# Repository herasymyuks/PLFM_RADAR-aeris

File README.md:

# AERIS-10: Open Source Pulse Linear Frequency Modulated Phased Array Radar

)

AERIS-10 is an open-source, low-cost 10.5 GHz phased array radar system featuring Pulse Linear Frequency Modulated (LFM) modulation. Available in two versions (3km and 20km range), it's designed for researchers, drone developers, and serious SDR enthusiasts who want to explore and experiment with phased array radar technology.

## 📡 Overview

The AERIS-10 project aims to democratize radar technology by providing a fully open-source, modular, and hackable radar system. Whether you're a university researcher, a drone startup, or an advanced maker, AERIS-10 offers a platform for experimenting with beamforming, pulse compression, Doppler processing, and target tracking.

## 🔬 Key Features

- **Open Source Hardware & Software** - Complete schematics, PCB layouts, firmware, and software available
- **Dual Version Availability**:
  - **AERIS-10N (Nexus)**: 3km range with 8x16 patch antenna array
  - **AERIS-10X (Extended)**: 20km range with 32x16 dielectric-filled slotted waveguide array
- **Full Electronic Beam Steering** - ±45° electronic steering in elevation and azimuth
- **Advanced Signal Processing** - On-board FPGA handles pulse compression, Doppler FFT, MTI, and CFAR
- **Python GUI** - User-friendly interface with map integration
- **GPS/IMU Integration** - Real-time position and attitude correction
- **Modular Design** - Separate power management, frequency synthesis, and RF boards

## 🏗️ System Architecture

### Hardware Components

The AERIS-10 main sub-systems are:

- **Power Management Board** - Supplies all necessary voltage levels to the electronics components with proper filtering and sequencing (sequencing ensured by the microcontroller)

- **Frequency Synthesizer Board** - Uses a high-performance Low Jitter Clock Generator (AD9523-1) that supplies phase-aligned clock references for:
  - RX and TX Frequency Synthesizers (ADF4382)
  - DAC
  - ADC
  - FPGA

- **Main Board** containing:
  - **DAC** - Generates the RADAR Chirps
  - **2x Microwave Mixers (LT5552)** - For up-conversion and IF-down-conversion
  - **4x 4-Channel Phase Shifters (ADAR1000)** - For RX and TX chain beamforming
  - **16x Front End Chips (ADTR1107)** - Used for both Low Noise Amplifying (RX) and Power Amplifying (TX) stages
  - **XC7A50T-2FTG256I FPGA** (per the Main Board schematic, U42; earlier documentation said XC7A100T — see `docs/FPGA/FPGA_PROJECT_RECONSTRUCTION.md`) - Handles RADAR Signal Processing:
    - PLFM Chirps generation via the DAC
    - Raw ADC data read
    - Automatic Gain Control (AGC)
    - I/Q Baseband Down-Conversion
    - Decimation
    - Filtering
    - Forward FFT
    - Pulse Compression
    - Doppler, MTI and CFAR processing
    - USB Interface
  - **STM32F746xx Microcontroller** - Used for:
    - Power-up and power-down sequencing (see Power Management Excel File)
    - FPGA communication
    - Setup and Interface with:
      - Clock Generator (AD9523-1)
      - 2x Frequency Synthesizers (ADF4382)
      - 4x 4-Channel Phase Shifters (ADAR1000) for RADAR pulse sequencing
      - 2x ADS7830 ADCs (on Power Amplifier Boards) for Idq measurement
      - 2x DAC5578 (on Power Amplifier Boards) for Vg control
      - GPS module for GUI map centering
      - GY-85 IMU for pitch/roll correction of target coordinates
      - BMP180 Barometer
      - Stepper Motor
      - 8x ADS7830 Temperature Sensors for cooling fan control
      - RF switches

- **16x Power Amplifier Boards** - Used only for AERIS-10E version, featuring 10Watt QPA2962 GaN amplifier for extended range

- **Antenna Arrays**:
  - **AERIS-10N (Nexus)** - 8x16 patch antenna array
  - **AERIS-10X (Extended)** - 32x16 dielectric-filled slotted waveguide antenna array

- **Miscellaneous Components**:
  - Slip-Ring
  - Stepper Motor and drivers
  - Cooling Fans
  - Enclosure) 

### Processing Pipeline

1. **Waveform Generation** - DAC creates LFM chirps
2. **Up/Down Conversion** - LT5552 mixers handle frequency translation
3. **Beam Steering** - ADAR1000 phase shifters control 16 elements
4. **Signal Processing (FPGA)**:
   - Raw ADC data capture
   - I/Q baseband down-conversion
   - Decimation & filtering (CIC/FIR)
   - Pulse compression
   - Doppler FFT processing
   - MTI & CFAR detection
5. **System Management (STM32)**:
   - Power sequencing
   - Peripheral configuration
   - GPS/IMU integration
   - Stepper motor control
6. **Visualization (Python GUI)**:
   - Real-time target plotting
   - Map integration
   - Radar control interface

## 📊 Technical Specifications

| Parameter | AERIS-10N (Nexus) | AERIS-10X (Extended) |
|-----------|-------------------|----------------------|
| **Frequency** | 10.5 GHz | 10.5 GHz |
| **Max Range** | 3 km | 20 km |
| **Antenna** | 8x16 Patch Array | 32x16 Slotted Waveguide |
| **Beam Steering** | Electronic (±45°) | Electronic (±45°) |
| **Mechanical Scan** | 360° (stepper motor) | 360° (stepper motor) |
| **Output Power** | ~1Wx16 | 10Wx16 (GaN amplifier) |
| **Processing** | FPGA + STM32 | FPGA + STM32 |

## 🚀 Getting Started

### Prerequisites

- Basic understanding of radar principles
- Experience with PCB assembly (for hardware build)
- Python 3.8+ for the GUI software
- FPGA development tools (Vivado) for signal processing modifications

### Hardware Assembly

1. **Order PCBs**: the designer-released EAGLE export does not exist in `4_Schematics and Boards Layout/4_7_Production Files` (only the Synthesizer P&P/BOM). KiCad-converted manufacturing packages (Gerber, drill, drawings, STEP, DRC) for all four boards are in `engineering/PCB/<BOARD>/` (status in each README — Main and Power Board layouts are unfinished in the source); BETA completions in `beta/pcb/`.
2. **Source Components**: bills of materials with reference designators in `docs/BOM/` (no manufacturer part numbers in the source schematics; BETA BOMs with proposed MPNs in `beta/pcb/`).
3. **Assembly**: `engineering/ASSEMBLY/ASSEMBLY_SEQUENCE.md`, `PARTS_LIST.md` and the CONCEPTUAL exploded view (the `10_docs/assembly_guide.md` referenced earlier was never committed).
4. **Antenna**: no antenna CAD exists in the repository; a PROPOSED 16×8 patch-array panel (KiCad) is in `engineering/DESIGN/ANTENNA/`.
5. **Enclosure**: no enclosure files exist (the `10_docs/Hardware/Enclosure` folder referenced earlier was never committed); a PROPOSED head/pedestal design (FreeCAD/STEP, drawings) is in `engineering/DESIGN/MECHANICAL/`.

> **Reconstruction status (2026-10-09):** see `docs/AERIS10_ENGINEERING_BUILD_MANUAL.md` (master manual), `engineering/DRAWING_REGISTER.md` and `beta/README.md`. Run `bash tools/run_all_checks.sh` for the current validation state.

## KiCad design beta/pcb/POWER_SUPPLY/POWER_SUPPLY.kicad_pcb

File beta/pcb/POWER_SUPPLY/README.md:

# Power Supply Board (PowerBoard) — BETA board

Project AERIS-10 · `beta/pcb/POWER_SUPPLY/` · 2026-10-09 · **Status: BETA — KiCad/Freerouting-routed, DRC-checked, NOT complete (89 connections still open, see `UNROUTED.md`), not reviewed by the original designer, not fabricated.**

Source of this copy: `engineering/PCB/POWER_SUPPLY/kicad/POWER_SUPPLY.kicad_pcb` (kicad-cli EAGLE import of `PowerBoard.brd`; 2 layers, 280 × 300 mm). The source layout was unfinished: 309 airwires and 132 of 320 footprints parked outside the outline (y = +77 … +701 mm).

## 1. Before / after

| Check | Before (engineering/PCB conversion) | After (BETA) |
|---|---|---|
| unconnected_items | 308 | 89 |
| clearance | 53 | 56 |
| drill_out_of_range | 8 | 8 |
| isolated_copper | 4 | 0 |
| silk_over_copper | 40 | 168 |
| silk_overlap | 22 | 65 |
| solder_mask_bridge | 8 | 8 |
| track_dangling | 4 | 2 |
| via_dangling | 0 | 20 |
| zones_intersect | 21 | 1 |
| **DRC violations total** | 160 | 328 |

Unconnected items 308 → **89** (−71 %). Footprints outside the outline 132 → **0**. Reports: `exports/reports/DRC_report.txt|json`.

## 2. What was changed (chronological, all logged)

| # | Change | Result | Tool / log |
|---|---|---|---|
| 1 | Netclass `Default`: track 0.25 mm, clearance 0.2 mm, via 0.5/0.3 mm (routing rule for new copper only) | — | `POWER_SUPPLY.kicad_pro` |
| 2 | 110 parts placed inside the outline in 29 net clusters next to the inside parts they connect to (1 mm grid, 3 mm edge margin, no overlap with existing parts/tracks/pours); 22 KK-254 connectors (`22-23-2021`) placed on the nearest board edge | 132 → 0 outside | `tools/beta_place_outside.py`, `placement_moves.json`, `placement_moves_connectors.json` |
| 3 | Freerouting 2.5.0 pass 1 (20 passes, existing 916 tracks/vias exported `(type fix)`), SES merged additively | +1336 tracks, +168 vias; unconnected 308 → 102 | `POWER_SUPPLY.dsn/.ses`, `freerouting.log`, `ses_merge.json` |
| 4 | 45 overlapping same-net zones re-prioritised; board-wide B.Cu GND zone `BETA_GND_plane_B.Cu` added (priority 0 — the EAGLE B.Cu GND polygon already covers the board, so it only fills remaining gaps) | zones_intersect 21 → 1 | `tools/beta_zone_priorities.py`, `tools/beta_add_plane.py` |
| 5 | Straight same-net bridges for the gaps in the DRC list, DRC, revert of every bridge that caused a clearance/crossing violation | 102 tried, 29 kept; 102 → 96 | `tools/beta_bridge_unconnected.py`, `bridges_pass1.json` |
| 6 | Freerouting pass 2 on the bridged board (12 passes) | +36 tracks, +3 vias; 96 → 96 | `POWER_SUPPLY_pass2.ses`, `freerouting_pass2.log`, `ses_merge_pass2.json` |
| 7 | GND stitching: vias where B.Cu GND islands overlap F.Cu GND fills, via next to unconnected GND pads; DRC-violating ones reverted | 50 tried, 22 kept; 96 → 89 | `tools/beta_gnd_stitch.py`, `stitch_gnd.json` |
| 8 | Refill, DRC, package export | | `tools/beta_drc.sh`, `tools/beta_export_package.sh`, `exports/EXPORT_LOG.md` |

## 3. What remains

* **89 unconnected items** — listed with reasons and a manual procedure in `UNROUTED.md` (49 GND, 10 VIN, rest on regulator outputs). Root causes: the EAGLE design distributes VIN/GND through separate local pours joined only by airwires (an autorouter does not connect pour to pour), and the autorouted bottom tracks fragment the B.Cu GND plane.
* DRC (`exports/reports/DRC_report.txt`): clearance 56 (0.15 mm pad-to-pad inside the ADM7151/TPS7A83 footprints and 3 N$ tracks of the source — footprint/library level, EAGLE DRU allowed 0.15 mm there), drill_out_of_range 8 (0.254 mm via-pads in the TPS7A8300 footprint vs DRU 0.3 mm min drill — footprint level, fab to confirm), silk_over_copper 168 / silk_overlap 65 (reference texts of the parts placed by script sit on their own pads — cosmetic, to be tidied with `tools/beta_silk_nudge.py` once routing is final), via_dangling 20 (autorouter vias whose second-side wire was dropped — remove with *Cleanup tracks & vias* once routing is final), solder_mask_bridge 8, track_dangling 2, zones_intersect 1.
* Placement by script is topological, not thermal/EMC: the regulator clusters sit where free space was nearest to their connectors. **A designer must review the placement** (inductor orientation, input/output capacitor proximity, heat spreading) before any routing clean-up.
* 24 pins without net in the schematic (`engineering/ELECTRICAL/netlists/POWER_SUPPLY_unresolved_connections.md`: TPS7A8300 feedback-select pins, LM2662 FC/OSC) are not a layout issue but must be dispositioned before fabrication.

## 4. Files

`POWER_SUPPLY.kicad_pcb` / `.kicad_pro` (BETA board), `BOM_POWER_SUPPLY_beta.csv` (7 HIGH / 18 MEDIUM / 3 LOW / 0 EMPTY lines), `FAB_NOTES.md`, `UNROUTED.md`, logs listed above, `exports/`.

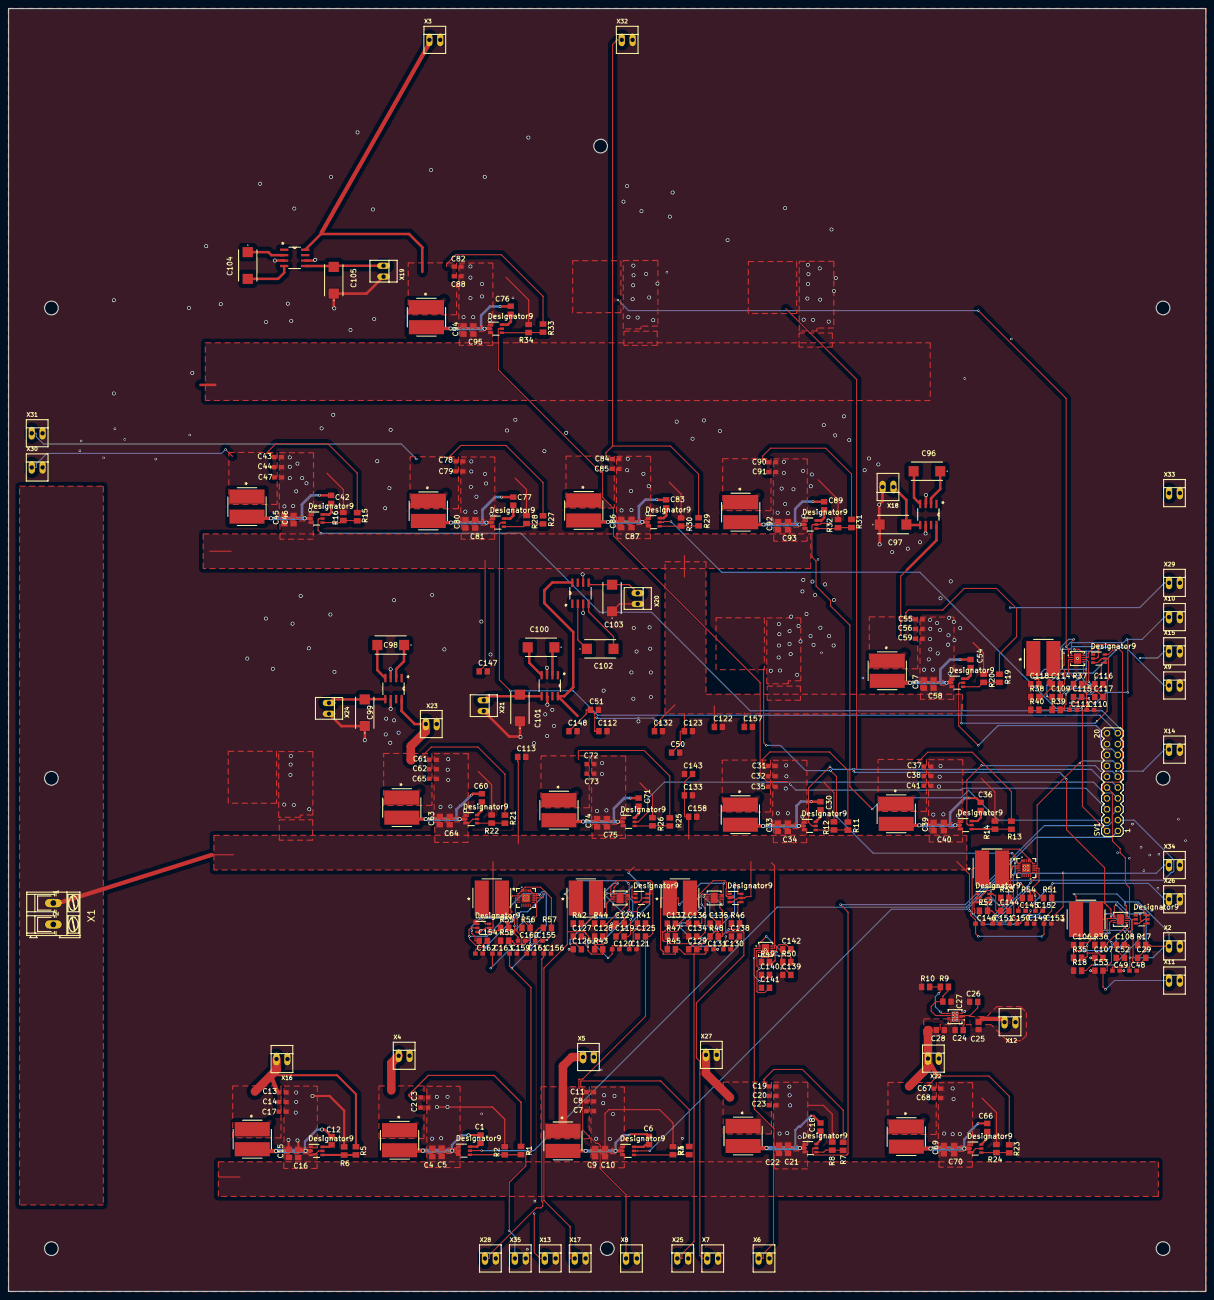
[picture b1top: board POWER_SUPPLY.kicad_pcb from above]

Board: 2 copper layers, 280.0 x 300.0 mm, 320 parts (0 on the bottom side), 156 nets.

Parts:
C1, C6, C12, C18, C29, C30, C36, C42, C54, C60, C66, C71, C76, C77, C83, C89, C109, C119, C129, C144, C154: 0.1µF; C0805
C2, C3, C7, C8, C11, C13, C14, C17, C19, C20, C23, C31, C32, C35, C37, C38, C41, C43, C44, C47, C48, C49, C55, C56, C59, C61, C62, C65, C67, C68, C72, C73, C78, C79, C82, C84, C85, C88, C90, C91, C110, C111, C120, C121, C130, C131, C145, C146, C149, C155, C156, C159: 22µF; C0603
C4, C5, C9, C10, C15, C16, C21, C22, C24, C25, C28, C33, C34, C39, C40, C45, C46, C50, C51, C52, C53, C57, C58, C63, C64, C69, C70, C74, C75, C80, C81, C86, C87, C92, C93, C94, C95, C108, C112, C113, C114, C115, C118, C122, C123, C124, C125, C128, C132, C133, C134, C135, C138, C139, C140, C143, C147, C148, C157, C158: 10µF; C0805
C26, C27, C106, C107, C116, C117, C126, C127, C136, C137, C141, C142: 1µF; C0805
C96, C97, C98, C99, C100, C101, C102, C103, C104, C105: T521W476M020ATE045; T521W
C150, C152, C160, C162: 10nF; C0603
C151, C153, C161, C163: 10µF; C0603
R1: 3.09k; M0805
R2, R4, R6, R8, R10, R12, R14, R16, R18, R20, R22, R24, R26, R28, R30, R32, R34, R36, R38, R40, R42, R44, R46, R48, R50, R52, R56: 10k; M0805
R3: 13.7k; M0805
R5, R7, R11, R13, R15, R19: 32.2k; M0805
R9, R35, R43, R47: 12k; M0805
R17, R23, R25, R27, R29, R31, R37, R41, R45, R51, R55: 56.2k; M0805
R21: 34.8k; M0805
R33: 61.9k; M0805
R39: 2k; M0805
R49: 23.4k; M0805
R53, R57: 35.7k; M0805
R54, R58: 11.5k; M0805
SV1: MA10-2
U1, U2, U3, U4, U6, U7, U8, U9, U10, U11, U12, U13, U14, U15, U16, U17, U24, U26, U28, U31, U33: TPS562208DDCT; DDC0006A_N
U5, U23, U25, U27, U29, U30: ADM7151ACPZ-04-R7; CP_8_11_ADI
U18, U19, U20, U21, U22: LM2662MX/NOPB; M08A
U32, U34: TPS7A8300RGRR; RGR20_2P05X2P05_TEX
U$1, U$2: 2.2µH; IND_VLP8040T-1R0N_TDK
U$3, U$4, U$5, U$6, U$7, U$8, U$9, U$10, U$11, U$12, U$13, U$14, U$15, U$16, U$17, U$18, U$19, U$20, U$21: 3.3µH; IND_VLP8040T-1R0N_TDK
UNK_HOLE_0: dummyfp0
UNK_HOLE_1: dummyfp1
UNK_HOLE_2: dummyfp2
UNK_HOLE_3: dummyfp3
UNK_HOLE_4: dummyfp4
UNK_HOLE_5: dummyfp5
UNK_HOLE_6: dummyfp6
UNK_HOLE_7: dummyfp7
X1: AK300_2
X2, X3, X4, X5, X6, X7, X8, X9, X10, X11, X12, X13, X14, X15, X16, X17, X18, X19, X20, X21, X22, X23, X24, X25, X26, X27, X28, X29, X30, X31, X32, X33, X34, X35: 22-23-2021

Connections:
+1V0_FPGA: C2.1, C3.1, R1.2, U$1.1, X4.1
+1V8_CLOCK: C115.2, U25.2, X10.1
+1V8_FPGA: C7.1, C8.1, C11.1, R3.2, U$2.1, X5.1
+3V3: C13.1, C14.1, C17.1, R5.2, U$3.1, X16.1
+3V3_ADAR_12: C31.1, C32.1, C35.1, R11.2, U$6.1, X14.1
+3V3_ADAR_34: C37.1, C38.1, C41.1, R13.2, U$7.1, X15.1
+3V3_ADTR: C149.1, R53.2, U32.1, U32.19, U32.20, X34.1
+3V3_AN: C25.2, U5.2, X12.1
+3V3_CLOCK: C53.2, U23.2, X11.1
+3V3_FPGA: C19.1, C20.1, C23.1, R7.2, U$4.1, X27.1
+3V3_LO_1: C125.2, U27.2, X8.1
+3V3_LO_2: C135.2, U29.2, X7.1
+3V3_SW: C55.1, C56.1, C59.1, R19.2, U18.8, U$10.1, X29.1
+3V3_VDD_SW: C43.1, C44.1, C47.1, R15.2, U$8.1, X30.1
+3V3_XO: C159.1, R57.2, U34.1, U34.19, U34.20, X35.1
+3V4: C61.1, C62.1, C65.1, R21.2, U19.8, U$11.1, X23.1
+5V0_0: C28.2, C67.1, C68.1, R23.2, U5.7, U5.8, U$12.1, X22.1
+5V0_1: C48.1, C49.1, C108.2, R17.2, U23.8, U$5.1, X2.1
+5V0_2: C110.1, C111.1, C118.2, R37.2, U25.8, U$9.1, X9.1
+5V0_3: C120.1, C121.1, C128.2, R41.2, U27.7, U27.8, U$18.1, X17.1
+5V0_4: C130.1, C131.1, C138.2, R45.2, U29.7, U29.8, U$19.1, X25.1
+5V0_5: C155.1, C156.1, C163.1, R55.2, U34.14, U34.15, U34.16, U34.17, U$21.1, X28.1
+5V0_ADAR: C72.1, C73.1, R25.2, U20.8, U21.8, U$13.1, X13.1
+5V0_ADTR: C145.1, C146.1, C153.1, R51.2, U32.15, U32.16, U32.17, U$20.1, X26.1
+5V0_LO: C140.2, U30.2, X6.1
+5V0_PA_1: C78.1, C79.1, R27.2, U$14.1, X31.1
+5V0_PA_2: C84.1, C85.1, R29.2, U$15.1, X32.1
+5V0_PA_3: C90.1, C91.1, R31.2, U$16.1, X33.1
+5V5_PA: C82.1, C88.1, R33.2, U22.8, U$17.1, X3.1
-3V3_SW: C97.2, U18.5, X18.1
-3V4: C99.2, U19.5, X24.1
-5V0_ADAR12: C101.2, U20.5, X21.1
-5V0_ADAR34: C103.2, U21.5, X20.1
-5V5_PA: C105.2, U22.5, X19.1
EN_+1V0_FPGA: SV1.1, U1.5
EN_+1V8_CLOCK: SV1.8, U25.7
EN_+1V8_FPGA: SV1.3, U2.5
EN_+3V3_ADAR12: SV1.9, U6.5
EN_+3V3_ADAR34: SV1.11, U7.5
EN_+3V3_ADTR: SV1.13, U32.14
EN_+3V3_CLOCK: SV1.10, U23.7
EN_+3V3_FPGA: SV1.5, U4.5
EN_+3V3_SW: SV1.15, U10.5
EN_+3V3_VDD_SW: SV1.17, U8.5
EN_+5V0_ADAR: SV1.7, U13.5
EN_+5V0_PA1: SV1.19, U14.5
EN_+5V0_PA2: SV1.2, U15.5
EN_+5V0_PA3: SV1.4, U16.5
EN_+5V5_PA: SV1.6, U17.5
GND: C2.2, C3.2, C4.2, C5.2, C7.2, C8.2, C9.2, C10.2, C11.2, C13.2, C14.2, C15.2, C16.2, C17.2, C19.2, C20.2, C21.2, C22.2, C23.2, C24.1, C25.1, C26.1, C27.1, C28.1, C31.2, C32.2, C33.2, C34.2, C35.2, C37.2, C38.2, C39.2, C40.2, C41.2, C43.2, C44.2, C45.2, C46.2, C47.2, C48.2, C49.2, C50.2, C51.2, C52.1, C53.1, C55.2, C56.2, C57.2, C58.2, C59.2, C61.2, C62.2, C63.2, C64.2, C65.2, C67.2, C68.2, C69.2, C70.2, C72.2, C73.2, C74.2, C75.2, C78.2, C79.2, C80.2, C81.2, C82.2, C84.2, C85.2, C86.2, C87.2, C88.2, C90.2, C91.2, C92.2, C93.2, C94.2, C95.2, C97.1, C99.1, C101.1, C103.1, C105.1, C106.1, C107.1, C108.1, C110.2, C111.2, C112.2, C113.2, C114.1, C115.1, C116.1, C117.1, C118.1, C120.2, C121.2, C122.2, C123.2, C124.1, C125.1, C126.1, C127.1, C128.1, C130.2, C131.2, C132.2, C133.2, C134.1, C135.1, C136.1, C137.1, C138.1, C139.1, C140.1, C141.1, C142.1, C143.1, C145.2, C146.2, C147.2, C148.2, C149.2, C151.2, C152.2, C153.2, C155.2, C156.2, C157.2, C158.2, C159.2, C161.2, C162.2, C163.2, R2.1, R4.1, R6.1, R8.1, R10.1, R12.1, R14.1, R16.1, R18.1, R20.1, R22.1, R24.1, R26.1, R28.1, R30.1, R32.1, R34.1, R36.1, R38.1, R40.1, R42.1, R44.1, R46.1, R48.1, R50.1, R52.1, R54.1, R56.1, R58.1, SV1.12, SV1.14, SV1.16, SV1.18, SV1.20, U1.1, U2.1, U3.1, U4.1, U5.4, U5.9, U6.1, U7.1, U8.1, U9.1, U10.1, U11.1, U12.1, U13.1, U14.1, U15.1, U16.1, U17.1, U18.3, U18.6, U19.3, U19.6, U20.3, U20.6, U21.3, U21.6, U22.3, U22.6, U23.4, U23.9, U24.1, U25.4, U25.9, U26.1, U27.4, U27.9, U28.1, U29.4, U29.9, U30.4, U30.9, U31.1, U32.8, U32.18, U32.21, U33.1, U34.8, U34.18, U34.21, X1.2, X2.2, X3.2, X4.2, X5.2, X6.2, X7.2, X8.2, X9.2, X10.2, X11.2, X12.2, X13.2, X14.2, X15.2, X16.2, X17.2, X18.2, X19.2, X20.2, X21.2, X22.2, X23.2, X24.2, X25.2, X26.2, X27.2, X28.2, X29.2, X30.2, X31.2, X32.2, X33.2, X34.2, X35.2
unnamed: C1.2, U1.2, U$1.2
unnamed: C1.1, U1.6
unnamed: C6.2, U2.2, U$2.2
unnamed: R1.1, R2.2, U1.4
unnamed: C6.1, U2.6
unnamed: R3.1, R4.2, U2.4
unnamed: C12.2, U3.2, U$3.2
unnamed: C12.1, U3.6
unnamed: R5.1, R6.2, U3.4
unnamed: C18.2, U4.2, U$4.2
unnamed: C18.1, U4.6
unnamed: R7.1, R8.2, U4.4
unnamed: C24.2, U5.1
unnamed: C139.2, U30.1
unnamed: C26.2, U5.3
unnamed: C30.2, U6.2, U$6.2
unnamed: C30.1, U6.6
unnamed: R11.1, R12.2, U6.4
unnamed: C36.2, U7.2, U$7.2
unnamed: C36.1, U7.6
unnamed: R13.1, R14.2, U7.4
unnamed: C42.2, U8.2, U$8.2
unnamed: C42.1, U8.6
unnamed: R15.1, R16.2, U8.4
unnamed: R9.1, R10.2, U5.5
unnamed: C29.2, U9.2, U$5.2
unnamed: C27.2, R9.2, U5.6
unnamed: C54.2, U10.2, U$10.2
unnamed: C54.1, U10.6
unnamed: R19.1, R20.2, U10.4
unnamed: C60.2, U11.2, U$11.2
unnamed: C60.1, U11.6
unnamed: R21.1, R22.2, U11.4
unnamed: C66.2, U12.2, U$12.2
unnamed: C66.1, U12.6
unnamed: R23.1, R24.2, U12.4
unnamed: C71.2, U13.2, U$13.2
unnamed: C71.1, U13.6
unnamed: R25.1, R26.2, U13.4
unnamed: C77.2, U14.2, U$14.2
unnamed: C77.1, U14.6
unnamed: R27.1, R28.2, U14.4
unnamed: C83.2, U15.2, U$15.2
unnamed: C83.1, U15.6
unnamed: R29.1, R30.2, U15.4
unnamed: C89.2, U16.2, U$16.2
unnamed: C89.1, U16.6
unnamed: R31.1, R32.2, U16.4
unnamed: C76.2, U17.2, U$17.2
unnamed: C76.1, U17.6
unnamed: R33.1, R34.2, U17.4
unnamed: C98.1, U19.2
unnamed: C98.2, U19.4
unnamed: C96.1, U18.2
unnamed: C96.2, U18.4
unnamed: C100.1, U20.2
unnamed: C100.2, U20.4
unnamed: C102.1, U21.2
unnamed: C102.2, U21.4
unnamed: C104.1, U22.2
unnamed: C104.2, U22.4
unnamed: C141.2, U30.3
unnamed: R49.1, R50.2, U30.5
unnamed: C29.1, U9.6
unnamed: R17.1, R18.2, U9.4
unnamed: C52.2, U23.1
unnamed: C142.2, R49.2, U30.6
unnamed: C106.2, U23.3
unnamed: R35.1, R36.2, U23.5
unnamed: C107.2, R35.2, U23.6
unnamed: C144.2, U31.2, U$20.2
unnamed: C144.1, U31.6
unnamed: C109.2, U24.2, U$9.2
unnamed: C109.1, U24.6
unnamed: R37.1, R38.2, U24.4
unnamed: C114.2, U25.1
unnamed: R51.1, R52.2, U31.4
unnamed: C116.2, U25.3
unnamed: R39.1, R40.2, U25.5
unnamed: C117.2, R39.2, U25.6
unnamed: C154.2, U33.2, U$21.2
unnamed: C150.1, U32.2
unnamed: C119.2, U26.2, U$18.2
unnamed: C119.1, U26.6
unnamed: R41.1, R42.2, U26.4
unnamed: C124.2, U27.1
unnamed: C154.1, U33.6
unnamed: C126.2, U27.3
unnamed: R43.1, R44.2, U27.5
unnamed: C127.2, R43.2, U27.6
unnamed: C150.2, R53.1, R54.2, U32.3
unnamed: C151.1, U32.12
unnamed: C129.2, U28.2, U$19.2
unnamed: C129.1, U28.6
unnamed: R45.1, R46.2, U28.4
unnamed: C134.2, U29.1
unnamed: R55.1, R56.2, U33.4
unnamed: C136.2, U29.3
unnamed: R47.1, R48.2, U29.5
unnamed: C137.2, R47.2, U29.6
unnamed: C152.1, U32.13
unnamed: C160.1, U34.2
unnamed: C160.2, R57.1, R58.2, U34.3
unnamed: C161.1, U34.12
unnamed: C162.1, U34.13
VIN: C4.1, C5.1, C9.1, C10.1, C15.1, C16.1, C21.1, C22.1, C33.1, C34.1, C39.1, C40.1, C45.1, C46.1, C50.1, C51.1, C57.1, C58.1, C63.1, C64.1, C69.1, C70.1, C74.1, C75.1, C80.1, C81.1, C86.1, C87.1, C92.1, C93.1, C94.1, C95.1, C112.1, C113.1, C122.1, C123.1, C132.1, C133.1, C143.2, C147.1, C148.1, C157.1, C158.1, U1.3, U2.3, U3.3, U3.5, U4.3, U6.3, U7.3, U8.3, U9.3, U9.5, U10.3, U11.3, U11.5, U12.3, U12.5, U13.3, U14.3, U15.3, U16.3, U17.3, U24.3, U24.5, U26.3, U26.5, U28.3, U28.5, U30.7, U30.8, U31.3, U31.5, U33.3, U33.5, X1.1

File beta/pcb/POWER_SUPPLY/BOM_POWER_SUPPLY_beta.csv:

item,qty,references,value,deviceset,device,package,manufacturer,mpn,mpn_confidence,dnp,note
1,34,X10 X11 X12 X13 X14 X15 X16 X17 X18 X19 X2 X20 X21 X22 X23 X24 X25 X26 X27 X28 X29 X3 X30 X31 X32 X33 X34 X35 X4 X5 X6 X7 X8 X9,,22-23-2021,,22-23-2021,Molex,22-23-2021,HIGH,no,"KK 254 header, 2 pos"
2,6,U23 U25 U27 U29 U30 U5,,ADM7151ACPZ-04-R7,,CP_8_11_ADI,Analog Devices,ADM7151ACPZ-04-R7,HIGH,no,"ultralow-noise LDO, LFCSP-8"
3,1,X1,,AK300/2,,AK300/2,PTR Messtechnik,AK300/2,HIGH,no,screw terminal 2 pos (library con-ptr500); verify current PTR part code AK300/2-5.0
4,21,C1 C109 C119 C12 C129 C144 C154 C18 C29 C30 C36 C42 C54 C6 C60 C66 C71 C76 C77 C83 C89,0.1µF,C-EU,C0805,C0805,Murata,GRM21BR71H104KA01L,MEDIUM,no,0805 X7R 50 V
5,4,C150 C152 C160 C162,10nF,C-EU,C0603,C0603,Murata,GRM188R71H103KA01D,MEDIUM,no,0603 X7R 50 V
6,60,C10 C108 C112 C113 C114 C115 C118 C122 C123 C124 C125 C128 C132 C133 C134 C135 C138 C139 C140 C143 C147 C148 C15 C157 C158 C16 C21 C22 C24 C25 C28 C33 C34 C39 C4 C40 C45 C46 C5 C50 C51 C52 C53 C57 C58 C63 C64 C69 C70 C74 C75 C80 C81 C86 C87 C9 C92 C93 C94 C95,10µF,C-EU,C0805,C0805,Murata,GRM21BR61E106KA73L,MEDIUM,no,0805 X5R 25 V
7,4,C151 C153 C161 C163,10µF,C-EU,C0603,C0603,Murata,GRM188R61E106MA73D,MEDIUM,no,0603 X5R 25 V
8,12,C106 C107 C116 C117 C126 C127 C136 C137 C141 C142 C26 C27,1µF,C-EU,C0805,C0805,Murata,GRM21BR71H105KA12L,MEDIUM,no,0805 X7R 50 V
9,52,C11 C110 C111 C120 C121 C13 C130 C131 C14 C145 C146 C149 C155 C156 C159 C17 C19 C2 C20 C23 C3 C31 C32 C35 C37 C38 C41 C43 C44 C47 C48 C49 C55 C56 C59 C61 C62 C65 C67 C68 C7 C72 C73 C78 C79 C8 C82 C84 C85 C88 C90 C91,22µF,C-EU,C0603,C0603,Murata,GRM188R60J226MEA0D,MEDIUM,no,0603 X5R 6.3 V — rail voltage to be verified
10,5,U18 U19 U20 U21 U22,,LM2662MX/NOPB,,M08A,Texas Instruments,LM2662MX/NOPB,HIGH,no,"switched-capacitor inverter, SOIC-8"
11,1,SV1,,MA10-2,,MA10-2,generic,TSW-110-07-G-D,LOW,no,EAGLE con-lstb MA10-2 = 2×10 pin header 2.54 mm; Samtec TSW-110-07-G-D proposed
12,2,U$1 U$2,2.2µH,POWER_INDUCTOR,,IND_VLP8040T-1R0N_TDK,TDK,VLP8040T-2R2M,MEDIUM,no,footprint is the VLP8040T 1R0N (1 µH) variant; value 2.2uH → same series part proposed
13,19,U$10 U$11 U$12 U$13 U$14 U$15 U$16 U$17 U$18 U$19 U$20 U$21 U$3 U$4 U$5 U$6 U$7 U$8 U$9,3.3µH,POWER_INDUCTOR,,IND_VLP8040T-1R0N_TDK,TDK,VLP8040T-3R3M,MEDIUM,no,footprint is the VLP8040T 1R0N (1 µH) variant; value 3.3uH → same series part proposed
14,27,R10 R12 R14 R16 R18 R2 R20 R22 R24 R26 R28 R30 R32 R34 R36 R38 R4 R40 R42 R44 R46 R48 R50 R52 R56 R6 R8,10k,R-EU_,M0805,M0805,Yageo,RC0805FR-0710KL,MEDIUM,no,1 % thick film
15,2,R54 R58,11.5k,R-EU_,M0805,M0805,Yageo,RC0805FR-0711K5L,MEDIUM,no,1 % thick film
16,4,R35 R43 R47 R9,12k,R-EU_,M0805,M0805,Yageo,RC0805FR-0712KL,MEDIUM,no,1 % thick film
17,1,R3,13.7k,R-EU_,M0805,M0805,Yageo,RC0805FR-0713K7L,MEDIUM,no,1 % thick film
18,1,R49,23.4k,R-EU_,M0805,M0805,Yageo,,LOW,no,non-E24/E96 value 23.4 Ω (nearest standard 2.32e+04 Ω) — value substitution is a design decision (Yageo RC0805FR-07 series)
19,1,R39,2k,R-EU_,M0805,M0805,Yageo,RC0805FR-072KL,MEDIUM,no,1 % thick film
20,1,R1,3.09k,R-EU_,M0805,M0805,Yageo,RC0805FR-073K09L,MEDIUM,no,1 % thick film
21,6,R11 R13 R15 R19 R5 R7,32.2k,R-EU_,M0805,M0805,Yageo,,LOW,no,non-E24/E96 value 32.2 Ω (nearest standard 3.24e+04 Ω) — value substitution is a design decision (Yageo RC0805FR-07 series)
22,1,R21,34.8k,R-EU_,M0805,M0805,Yageo,RC0805FR-0734K8L,MEDIUM,no,1 % thick film
23,2,R53 R57,35.7k,R-EU_,M0805,M0805,Yageo,RC0805FR-0735K7L,MEDIUM,no,1 % thick film
24,11,R17 R23 R25 R27 R29 R31 R37 R41 R45 R51 R55,56.2k,R-EU_,M0805,M0805,Yageo,RC0805FR-0756K2L,MEDIUM,no,1 % thick film
25,1,R33,61.9k,R-EU_,M0805,M0805,Yageo,RC0805FR-0761K9L,MEDIUM,no,1 % thick film
26,10,C100 C101 C102 C103 C104 C105 C96 C97 C98 C99,,T521W476M020ATE045,,T521W,KEMET,T521W476M020ATE045,HIGH,no,"polymer tantalum 47 µF 20 V, case W"
27,21,U1 U10 U11 U12 U13 U14 U15 U16 U17 U2 U24 U26 U28 U3 U31 U33 U4 U6 U7 U8 U9,,TPS562208DDCT,,DDC0006A_N,Texas Instruments,TPS562208DDCT,HIGH,no,"2 A buck converter, SOT-23-6"
28,2,U32 U34,,TPS7A8300RGRR,,RGR20_2P05X2P05_TEX,Texas Instruments,TPS7A8300RGRR,HIGH,no,"2 A LDO, VQFN-20"

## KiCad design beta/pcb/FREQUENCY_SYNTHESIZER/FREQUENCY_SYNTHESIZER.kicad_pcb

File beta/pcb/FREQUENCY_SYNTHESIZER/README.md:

# Frequency Synthesizer (Clocks_Freq_Synth_board) — BETA board

Project AERIS-10 · `beta/pcb/FREQUENCY_SYNTHESIZER/` · 2026-10-09 · **Status: BETA — KiCad-checked, silkscreen-cleaned, not reviewed by the original designer, not fabricated.**

Source of this copy: `engineering/PCB/FREQUENCY_SYNTHESIZER/kicad/FREQUENCY_SYNTHESIZER.kicad_pcb` (kicad-cli EAGLE import of `Clocks_Freq_Synth_board.brd`). Copper was **not modified** (fully routed in the source, 0 unconnected).

## 1. Before / after

| Check | Before (engineering/PCB conversion) | After (BETA) |
|---|---|---|
| unconnected_items | 0 | 0 |
| courtyards_overlap | 7 | 7 |
| silk_over_copper | 199 | 199 |
| silk_overlap | 199 | 199 |
| solder_mask_bridge | 199 | 199 |
| track_dangling | 35 | 35 |
| **DRC violations total** | 639 | 639 |

The silkscreen and mask counts are capped at 199 by KiCad; uncapped measurements and the classification of every type are in `DRC_DISPOSITION.md` (cosmetic silk/mask vs. real). Real items for review: 7 courtyard overlaps.

## 2. What was changed

| # | Change | Tool / log |
|---|---|---|
| 1 | 43 silkscreen reference texts moved to the nearest free position (≤ 3 mm, 0.05 mm step; copper untouched) | `tools/beta_silk_nudge.py`, `silk_nudges.json`; 103 texts still in conflict → `silk_conflicts_remaining.json` |
| 2 | Zones refilled, DRC re-run, package exported | `tools/beta_drc.sh`, `tools/beta_export_package.sh`, `exports/EXPORT_LOG.md` |

## 3. What remains

See `DRC_DISPOSITION.md`: 7 courtyard overlaps (review), 35 GND arc stubs (cosmetic), silk/mask items (cosmetic / fab CAM). Recommendation for the production revision: hide 0201 reference designators on silk.

## 4. Files

`FREQUENCY_SYNTHESIZER.kicad_pcb` / `.kicad_pro` / `_from_eagle.kicad_dru`, `BOM_FREQUENCY_SYNTHESIZER_beta.csv` (10 HIGH / 22 MEDIUM / 6 LOW / 2 EMPTY lines), `FAB_NOTES.md` (6-layer RO4350B/FR-4 stack-up proposal, 50 Ω / 100 Ω geometry measured w = 0.204 mm, s = 0.26 mm), `DRC_DISPOSITION.md`, `exports/`.

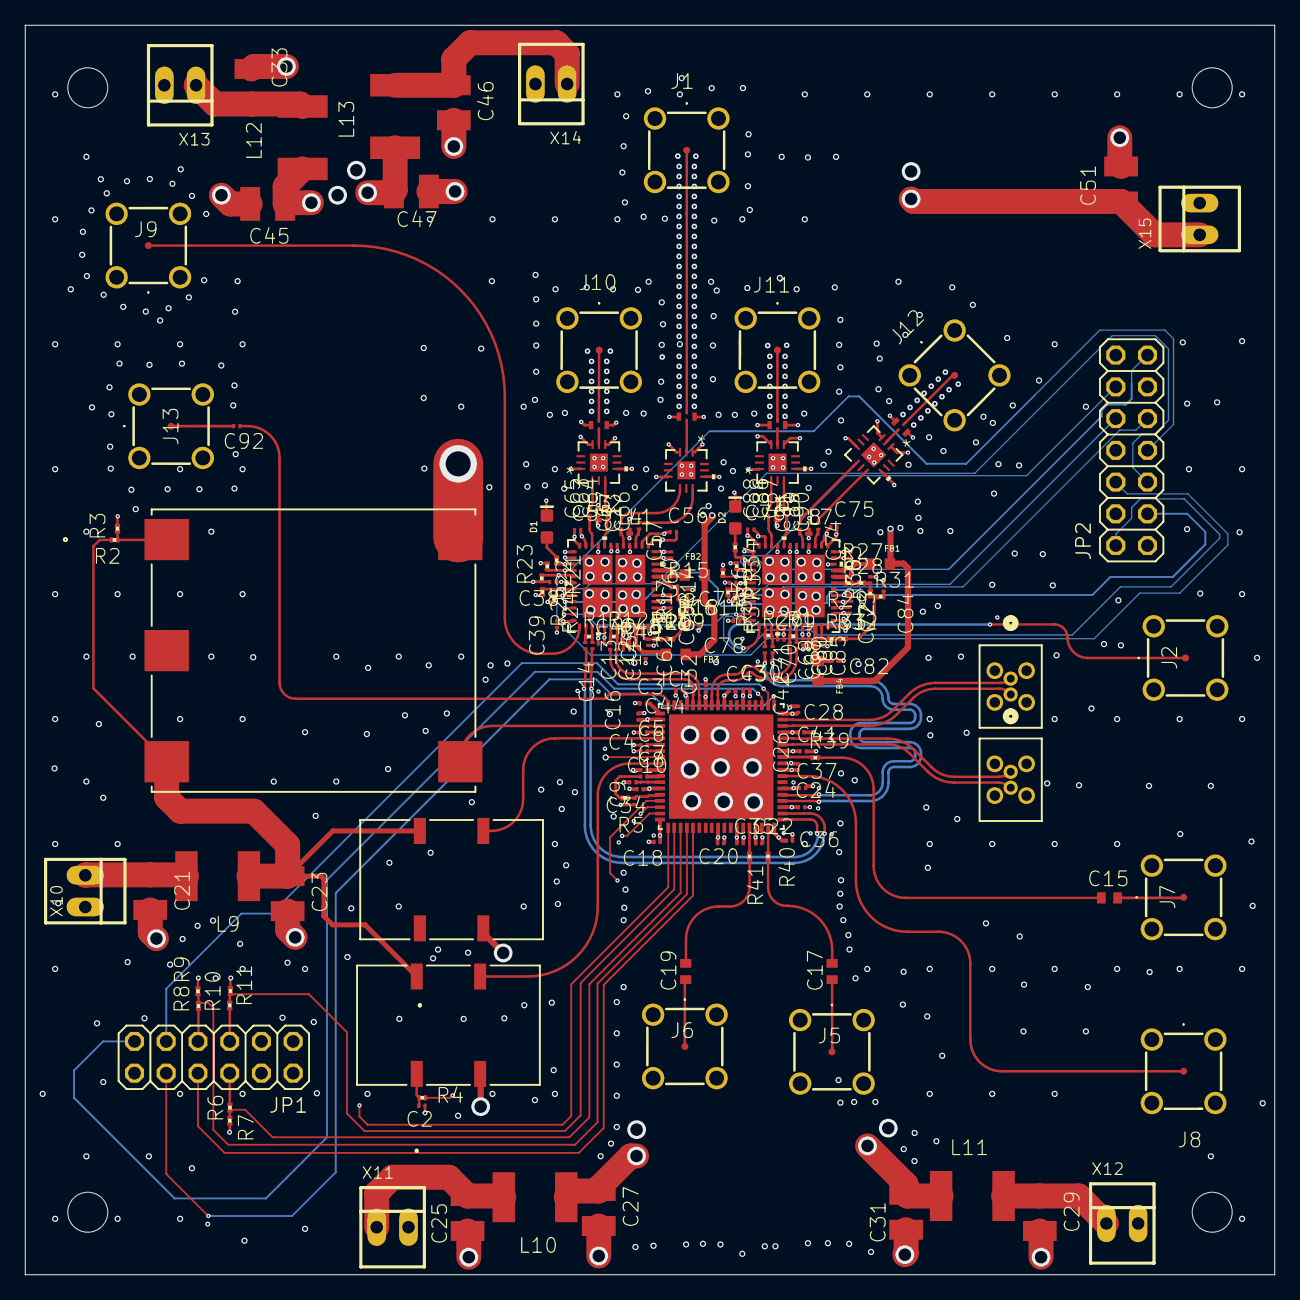
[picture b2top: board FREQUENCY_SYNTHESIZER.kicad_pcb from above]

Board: 6 copper layers, 100.0 x 100.0 mm, 188 parts (0 on the bottom side), 134 nets.

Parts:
C1, C62, C63, C85, C86, C89: 10pF; C0201
C2, C6: 0.33µF; C0201
C3: 0.47µf; C0201
C4, C5, C7: C0201
C8: 1000pF; C0201
C9, C10: 0.47µF; C0201
C11, C12, C13, C14, C59, C68, C69, C70, C71, C82: 1µF; C0201
C15, C17, C19: 10nF; C0402
C16, C18, C20, C22, C24, C26, C28, C30, C32, C34, C35, C36, C37, C41, C42, C43, C44, C64, C65, C66, C67, C87, C88, C90, C91: 0.1µF; C0201
C21, C25, C29, C33, C46, C51: 22µF; C1210
C23, C27, C31, C45, C47: 10µF; C1210
C38, C39, C40, C48, C49, C50, C55, C56, C57, C58, C72, C73, C74, C75, C76, C77, C78, C79, C80, C81: 4.7µF; C0201
C60, C83: 31pF; C0201
C61, C84: 10nF; C0201
C92: 0.1µf; C0201
D1, D2: Green; LED-0603
FB1, FB2, FB3, FB4: FBMH1608HL601-T; BEADC1608X90N
IC1: AD9523BCPZ; QFN50P1000X1000X100-73N
J1, J2, J5, J6, J7, J8, J9, J10, J11, J12, J13: 142-0731-211; 1420731211
J3, J4: CJT-T-P-HH-ST-TH1; CONN_CJT-T-P-XX-ST-TH1_SAI
JP1: 2X06
JP2: 2X07
L1, L2, L3, L4, L5, L6, L7, L8: 1.3nH; L0201
L9, L10, L11, L12, L13: L5650M
R1, R12, R13, R26: 100R; R0201
R2, R3, R4, R7, R9, R11: 1k; R0201
R5, R14, R15, R19, R20, R27, R28, R32, R33: 0R; R0201
R6, R8, R10: 0.65k; R0201
R16, R29: 931R; R0201
R17, R30: 30R; R0201
R18, R31: 330R; R0201
R21, R34: 500R; R0201
R22, R23, R24, R25, R35, R36, R37, R38: 200k; R0201
R39, R40, R41: 22R; R0201
U1, U6: ADF4382ABCCZ; CC-48-10_ADI
U2, U3, U7, U9: MTX2-143+; DQ1225_MNC
U4, U5, U8, U10: ATS1005-3DB-FD-T05; SMT_DB-FD-T05_SUS
UNK_HOLE_0: dummyfp0
UNK_HOLE_1: dummyfp1
UNK_HOLE_2: dummyfp2
UNK_HOLE_3: dummyfp3
X4: ECOC-2522-100.000-3HC; SMD5_ECOC-2522_25P4X22_ECS
X5, X6: CVHD-950-50.000; SMD4_CVHD-950_CRX
X10, X11, X12, X13, X14, X15: 22-23-2021

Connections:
10MHZ_OUT: IC1.3, X4.4
100MHZ_OUT: IC1.5, X5.3
+1V8_CLOCK: C31.1, C35.1, C36.1, C37.1, C41.1, C42.1, C43.1, C44.1, IC1.30, IC1.36, IC1.42, IC1.48, IC1.54, IC1.63, IC1.69, L11.1
+3V3_CLOCK: C16.1, C18.1, C20.1, C22.1, C24.1, C26.1, C27.1, C28.1, C30.1, C32.1, C34.1, IC1.2, IC1.13, IC1.18, IC1.27, IC1.33, IC1.39, IC1.45, IC1.51, IC1.60, IC1.66, L10.1
+3V3_LO_1: C38.1, C39.1, C40.1, C45.1, C48.1, C49.1, C50.1, C72.1, C77.1, C78.1, C79.1, C80.1, C81.1, L12.1, R24.2, R25.2, R37.2, R38.2, U1.3, U1.30, U1.36, U1.40, U1.44, U1.45, U6.3, U6.30, U6.36, U6.40, U6.44, U6.45
+3V3_LO_2: C1.1, C47.1, C55.1, C56.1, C57.1, C58.1, C63.1, C73.1, C74.1, C75.1, C76.1, C86.1, C89.1, L1.1, L2.1, L3.2, L4.2, L5.1, L6.2, L7.1, L8.2, L13.1, U1.5, U1.11, U1.13, U1.24, U6.5, U6.11, U6.13, U6.24
+3V3_XO: C23.1, L9.1, R2.2, X4.3, X5.4, X6.4
+5V0_LO: C51.1, FB1.1, FB2.1, FB3.2, FB4.2, X15.1
AD9523_CS: JP1.5, R10.1
AD9523_EEPROM_SEL: IC1.57, JP1.11
AD9523_OUT0_N: C11.2, IC1.67
AD9523_OUT0_P: C12.2, IC1.68
AD9523_OUT1_N: C68.2, IC1.64
AD9523_OUT1_P: C69.2, IC1.65
AD9523_OUT4_N: IC1.52, J3.2
AD9523_OUT4_P: IC1.53, J3.1
AD9523_OUT5_N: IC1.49, J4.2
AD9523_OUT5_P: IC1.50, J4.1
AD9523_OUT6+: C15.2, J7.1
AD9523_OUT7+: IC1.44, J8.1
AD9523_OUT8_N: C70.2, IC1.40
AD9523_OUT8_P: C71.2, IC1.41
AD9523_OUT9_N: C13.2, IC1.37
AD9523_OUT9_P: C14.2, IC1.38
AD9523_OUT10+: IC1.35, R40.1
AD9523_OUT11+: IC1.32, R41.1
AD9523_PD: IC1.15, JP1.1
AD9523_REF_SEL: IC1.16, JP1.2
AD9523_RESET: IC1.19, JP1.4
AD9523_SCLK: JP1.6, R6.1
AD9523_SDIO: JP1.7, R8.1
AD9523_SDO: IC1.23, JP1.8
AD9523_STATUS0: IC1.56, JP1.9
AD9523_STATUS1: IC1.55, JP1.10
AD9523_SYNC: IC1.17, JP1.3
ADF4382_RX_CE: JP2.10, R38.1, U6.31
ADF4382_RX_CS: JP2.9, R37.1, U6.32
ADF4382_RX_DELADJ: JP2.12, R35.2, U6.28
ADF4382_RX_DELSTR: JP2.11, R36.2, U6.29
ADF4382_RX_LKDET: JP2.13, R34.2, U6.27
ADF4382_RX_SYNC_N: C70.1, R26.2, U6.39
ADF4382_RX_SYNC_P: C71.1, R26.1, U6.38
ADF4382_SCLK: JP2.2, U1.34, U6.34
ADF4382_SDIO: JP2.3, U1.33, U6.33
ADF4382_SDO: JP2.1, U1.35, U6.35
ADF4382_TX_CE: JP2.5, R25.1, U1.31
ADF4382_TX_CS: JP2.4, R24.1, U1.32
ADF4382_TX_DELADJ: JP2.7, R22.2, U1.28
ADF4382_TX_DELSTR: JP2.6, R23.2, U1.29
ADF4382_TX_LKDET: JP2.8, R21.2, U1.27
ADF4382_TX_SYNC_N: C13.1, R13.2, U1.39
ADF4382_TX_SYNC_P: C14.1, R13.1, U1.38
GND: C1.2, C2.2, C3.1, C4.1, C5.1, C6.1, C7.1, C9.1, C10.1, C16.2, C18.2, C20.2, C21.2, C22.2, C23.2, C24.2, C25.2, C26.2, C27.2, C28.2, C29.2, C30.2, C31.2, C32.2, C33.2, C34.2, C35.2, C36.2, C37.2, C38.2, C39.2, C40.2, C41.2, C42.2, C43.2, C44.2, C45.2, C46.2, C47.2, C48.2, C49.2, C50.2, C51.2, C55.2, C56.2, C57.2, C58.2, C59.1, C60.2, C61.2, C62.2, C63.2, C72.2, C73.2, C74.2, C75.2, C76.2, C77.2, C78.2, C79.2, C80.2, C81.2, C82.1, C83.2, C84.2, C85.2, C86.2, C89.2, D1.C, D2.C, IC1.73, J1.2, J1.3, J1.4, J1.5, J2.2, J2.3, J2.4, J2.5, J5.2, J5.3, J5.4, J5.5, J6.2, J6.3, J6.4, J6.5, J7.2, J7.3, J7.4, J7.5, J8.2, J8.3, J8.4, J8.5, J9.2, J9.3, J9.4, J9.5, J10.2, J10.3, J10.4, J10.5, J11.2, J11.3, J11.4, J11.5, J12.2, J12.3, J12.4, J12.5, J13.2, J13.3, J13.4, J13.5, JP1.12, JP2.14, R3.1, R7.2, R9.2, R11.2, R22.1, R23.1, R35.1, R36.1, U1.1, U1.2, U1.4, U1.10, U1.12, U1.14, U1.16, U1.18, U1.19, U1.21, U1.23, U1.25, U1.26, U1.41, U1.48, U1.49, U1.50, U1.51, U1.52, U2.1, U2.3, U2.6, U2.10, U2.13, U3.1, U3.3, U3.6, U3.10, U3.13, U4.3, U4.4, U5.3, U5.4, U6.1, U6.2, U6.4, U6.10, U6.12, U6.14, U6.16, U6.18, U6.19, U6.21, U6.23, U6.25, U6.26, U6.41, U6.48, U6.49, U6.50, U6.51, U6.52, U7.1, U7.3, U7.6, U7.10, U7.13, U8.3, U8.4, U9.1, U9.3, U9.6, U9.10, U9.13, U10.3, U10.4, X4.5, X5.2, X6.2, X10.2, X11.2, X12.2, X13.2, X14.2, X15.2
unnamed: R2.1, R3.2, X4.1
unnamed: C2.1, R4.1, X6.1
unnamed: C3.2, IC1.1
unnamed: C6.2, IC1.7
unnamed: C4.2, IC1.4
unnamed: C5.2, IC1.6
unnamed: C7.2, IC1.10
unnamed: C8.2, IC1.11
unnamed: C8.1, R5.1
unnamed: C9.2, IC1.14, R5.2
unnamed: C10.2, IC1.12
unnamed: IC1.21, R6.2, R7.1
unnamed: IC1.22, R8.2, R9.1
unnamed: IC1.20, R10.2, R11.1
unnamed: C11.1, R12.2, U1.43
unnamed: C12.1, R12.1, U1.42
unnamed: C61.1, R18.2
unnamed: R14.1, U1.9
unnamed: FB2.2, R14.2, U1.8
unnamed: C59.2, FB3.1, U1.46
unnamed: R19.1, R20.2
unnamed: R15.1, U1.7
unnamed: R15.2, R16.2
unnamed: C60.1, R16.1, R17.2
unnamed: R17.1, R18.1, R19.2
unnamed: C62.1, R20.1, U1.47
unnamed: U2.2, U4.1
unnamed: C65.2, U2.7
unnamed: J10.1, U4.2
unnamed: C64.2, U2.9
unnamed: C67.2, U3.7
unnamed: C66.2, U3.9
unnamed: U3.2, U5.1
unnamed: J1.1, U5.2
unnamed: D1.A, R21.1
unnamed: J9.1, U1.37
unnamed: C68.1, R1.2, U6.43
unnamed: C69.1, R1.1, U6.42
unnamed: R27.1, U6.9
unnamed: FB1.2, R27.2, U6.8
unnamed: C82.2, FB4.1, U6.46
unnamed: C84.1, R31.2
unnamed: R32.1, R33.2
unnamed: R28.1, U6.7
unnamed: R28.2, R29.2
unnamed: C83.1, R29.1, R30.2
unnamed: R30.1, R31.1, R32.2
unnamed: C85.1, R33.1, U6.47
unnamed: D2.A, R34.1
unnamed: J2.1, U6.37
unnamed: C88.2, U7.7
unnamed: C87.2, U7.9
unnamed: U7.2, U8.1
unnamed: J11.1, U8.2
unnamed: C91.2, U9.7
unnamed: C90.2, U9.9
unnamed: U9.2, U10.1
unnamed: J12.1, U10.2
unnamed: C92.1, IC1.72
unnamed: C92.2, J13.1
unnamed: IC1.47, R39.1
unnamed: C15.1, R39.2
unnamed: C17.2, J5.1
unnamed: C17.1, R40.2
unnamed: C19.2, J6.1
unnamed: C19.1, R41.2
unnamed: C21.1, L9.2, X10.1
unnamed: C25.1, L10.2, X11.1
unnamed: C29.1, L11.2, X12.1
unnamed: C33.1, L12.2, X13.1
unnamed: C46.1, L13.2, X14.1
OSC_CTRL: IC1.8, R4.2
RX_RFOUT_1_N: C87.1, L5.2, U6.20
RX_RFOUT_1_P: C88.1, L6.1, U6.22
RX_RFOUT_2_N: C90.1, L7.2, U6.15
RX_RFOUT_2_P: C91.1, L8.1, U6.17
TX_RFOUT_1_N: C64.1, L2.2, U1.20
TX_RFOUT_1_P: C65.1, L3.1, U1.22
TX_RFOUT_2_N: C66.1, L1.2, U1.15
TX_RFOUT_2_P: C67.1, L4.1, U1.17
VCXO_OUT: IC1.9, X6.3

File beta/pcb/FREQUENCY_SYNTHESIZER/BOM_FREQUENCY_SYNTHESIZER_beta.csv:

item,qty,references,value,deviceset,device,package,manufacturer,mpn,mpn_confidence,dnp,note
1,11,J1 J10 J11 J12 J13 J2 J5 J6 J7 J8 J9,,142-0731-211,,1420731211,Cinch Connectivity (Johnson),142-0731-211,HIGH,no,SMA end-launch jack
2,6,X10 X11 X12 X13 X14 X15,,22-23-2021,,22-23-2021,Molex,22-23-2021,HIGH,no,"KK 254 header, 2 pos"
3,1,IC1,,AD9523BCPZ,,QFN50P1000X1000X100-73N,Analog Devices,AD9523BCPZ,HIGH,no,"clock generator, LFCSP-72"
4,2,U1 U6,,ADF4382ABCCZ,,CC-48-10_ADI,Analog Devices,ADF4382ABCCZ,HIGH,no,"PLL/VCO synthesizer, LGA-48"
5,4,U10 U4 U5 U8,,ATS1005-3DB-FD-T05,,SMT_DB-FD-T05_SUS,Susumu (per package suffix _SUS — verify),ATS1005-3DB-FD-T05,HIGH,no,SMT attenuator 3 dB
6,3,C4 C5 C7,,C-EU,C0201,C0201,,,EMPTY,no,no value in the schematic (C-EU / C0201) — cannot propose a part
7,25,C16 C18 C20 C22 C24 C26 C28 C30 C32 C34 C35 C36 C37 C41 C42 C43 C44 C64 C65 C66 C67 C87 C88 C90 C91,0.1µF,C-EU,C0201,C0201,Murata,GRM033R61A104KE15D,MEDIUM,no,0201 X5R 10 V
8,1,C92,0.1µf,C-EU,C0201,C0201,Murata,GRM033R61A104KE15D,MEDIUM,no,0201 X5R 10 V
9,2,C2 C6,0.33µF,C-EU,C0201,C0201,Murata,GRM033R60J334KE90D,MEDIUM,no,0201 X5R 6.3 V — voltage vs net to be verified
10,2,C10 C9,0.47µF,C-EU,C0201,C0201,Murata,GRM033R60J474KE90D,MEDIUM,no,0201 X5R 6.3 V — voltage vs net to be verified
11,1,C3,0.47µf,C-EU,C0201,C0201,Murata,GRM033R60J474KE90D,MEDIUM,no,0201 X5R 6.3 V — voltage vs net to be verified
12,1,C8,1000pF,C-EU,C0201,C0201,Murata,GRM033R71C102KA01D,MEDIUM,no,0201 X7R 16 V
13,3,C15 C17 C19,10nF,C-EU,C0402,C0402,Murata,GRM155R71H103KA01D,MEDIUM,no,0402 X7R (50 V / 16 V for 100 nF)
14,2,C61 C84,10nF,C-EU,C0201,C0201,Murata,GRM033R71C103KA01D,MEDIUM,no,0201 X7R 16 V
15,6,C1 C62 C63 C85 C86 C89,10pF,C-EU,C0201,C0201,Murata,GRM0335C1H100JA01D,MEDIUM,no,0201 C0G 50 V
16,5,C23 C27 C31 C45 C47,10µF,C-EU,C1210,C1210,Murata,GRM32ER71E106KA12L,MEDIUM,no,1210 X7R 25 V
17,10,C11 C12 C13 C14 C59 C68 C69 C70 C71 C82,1µF,C-EU,C0201,C0201,Murata,GRM033R60J105MEA2D,MEDIUM,no,0201 X5R 6.3 V — voltage vs net to be verified
18,6,C21 C25 C29 C33 C46 C51,22µF,C-EU,C1210,C1210,Murata,GRM32ER61E226KE15L,MEDIUM,no,1210 X5R 25 V
19,2,C60 C83,31pF,C-EU,C0201,C0201,Murata,,LOW,no,"non-E24 capacitance 31pF (nearest standard 30.9 pF) — value substitution is a design decision, designer to choose"
20,20,C38 C39 C40 C48 C49 C50 C55 C56 C57 C58 C72 C73 C74 C75 C76 C77 C78 C79 C80 C81,4.7µF,C-EU,C0201,C0201,Murata,GRM033R60G475ME47D,LOW,no,0201 X5R 4 V — only a few vendors offer >1 µF in 0201; verify availability and net voltage
21,2,J3 J4,,CJT-T-P-HH-ST-TH1,,CONN_CJT-T-P-XX-ST-TH1_SAI,Samtec (per package suffix _SAI — verify),CJT-T-P-HH-ST-TH1,HIGH,no,connector; manufacturer inferred from library suffix
22,2,X5 X6,,CVHD-950-50.000,,SMD4_CVHD-950_CRX,Crystek,CVHD-950-50.000,HIGH,no,OCXO/VCXO 50 MHz
23,1,X4,,ECOC-2522-100.000-3HC,,SMD5_ECOC-2522_25P4X22_ECS,ECS Inc.,ECOC-2522-100.000-3HC,HIGH,no,OCXO 100 MHz
24,4,FB1 FB2 FB3 FB4,,FBMH1608HL601-T,,BEADC1608X90N,Taiyo Yuden,FBMH1608HL601-T,HIGH,no,"ferrite bead 0603, 600 Ω"
25,5,L10 L11 L12 L13 L9,,L-EU,L5650M,L5650M,,,EMPTY,no,no value in the schematic (L-EU / L5650M) — cannot propose a part
26,8,L1 L2 L3 L4 L5 L6 L7 L8,1.3nH,L-US,L0201,L0201,Murata,LQP03TN1N3B02D,MEDIUM,no,0201 thin-film inductor
27,2,D1 D2,Green,LED-GREEN,-0603-WE,LED-0603,Würth,150060GS75000,MEDIUM,no,green LED 0603
28,4,U2 U3 U7 U9,,MTX2-143+,,DQ1225_MNC,Mini-Circuits,MTX2-143+,HIGH,no,RF transformer
29,1,JP1,,PINHD-2X6,,2X06,generic,61301221121,LOW,no,Würth 2.54 mm 2×6 header proposed
30,1,JP2,,PINHD-2X7,,2X07,generic,61301421121,LOW,no,Würth 2.54 mm 2×7 header proposed
31,3,R10 R6 R8,0.65k,R-EU_,R0201,R0201,Yageo,,LOW,no,non-E24/E96 value 0.65 Ω (nearest standard 649 Ω) — value substitution is a design decision (Yageo RC0201FR-07 series)
32,9,R14 R15 R19 R20 R27 R28 R32 R33 R5,0R,R-EU_,R0201,R0201,Yageo,RC0201JR-070RL,MEDIUM,no,jumper 0 Ω
33,4,R1 R12 R13 R26,100R,R-EU_,R0201,R0201,Yageo,RC0201FR-07100RL,MEDIUM,no,1 % thick film
34,6,R11 R2 R3 R4 R7 R9,1k,R-EU_,R0201,R0201,Yageo,RC0201FR-071KL,MEDIUM,no,1 % thick film
35,8,R22 R23 R24 R25 R35 R36 R37 R38,200k,R-EU_,R0201,R0201,Yageo,RC0201FR-07200KL,MEDIUM,no,1 % thick film
36,3,R39 R40 R41,22R,R-EU_,R0201,R0201,Yageo,RC0201FR-0722RL,MEDIUM,no,1 % thick film
37,2,R17 R30,30R,R-EU_,R0201,R0201,Yageo,RC0201FR-0730RL,MEDIUM,no,1 % thick film
38,2,R18 R31,330R,R-EU_,R0201,R0201,Yageo,RC0201FR-07330RL,MEDIUM,no,1 % thick film
39,2,R21 R34,500R,R-EU_,R0201,R0201,Yageo,,LOW,no,non-E24/E96 value 500 Ω (nearest standard 499 Ω) — value substitution is a design decision (Yageo RC0201FR-07 series)
40,2,R16 R29,931R,R-EU_,R0201,R0201,Yageo,RC0201FR-07931RL,MEDIUM,no,1 % thick film

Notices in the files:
beta/stm32/Core/Src/main.cpp:
Copyright (c) 2025 STMicroelectronics.
All rights reserved.
This software is licensed under terms that can be found in the LICENSE file
README.md:
License: MIT
